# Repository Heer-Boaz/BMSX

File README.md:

# BMSX

BMSX is an emulated machine with real emulator discipline.

BMSX is documented and implemented as if it were an obscure physical console:
carts run against CPU, RAM/ROM, MMIO registers, and device controllers. Host
code exists to present audio, video, input, files, and platform entrypoints; it
should not become the cart-facing hardware contract.

The TypeScript implementation builds a JavaScript machine runtime plus browser
and Node hosts. The C++ implementation mirrors the machine structure and supplies C++ machine and host artifacts.

The technical manuals specify the console. See `docs/architecture.md` only for
internal software ownership, dependencies and host/tooling boundaries.

## Setup

- Node.js 22 or later
- `npm ci --include=dev`
- Linux/WSL native requirements: see the [first-build prerequisites](docs/programming/getting-started.md#prerequisites).

## First cartridge and hardware reference

Start with [Build and inspect example cartridges](docs/programming/getting-started.md)
for a visible GPU picture, source layout and project-tool commands. That companion
describes this repository, not a manufacturer-mandated SDK. The working manual
series separates three scopes:

- **Book I — System and Hardware Reference:** begin with the
  [System overview](docs/book1/console.md), then follow its links to the owning
  hardware chapters and [Memory and bus access](docs/book1/memory.md).
- **Book II — BLua32 and BIOS Reference:** begin with
  [CPU and BLua32 instructions](docs/book1/cpu.md),
  [BLua source programs and extensions](docs/book1/blua-programs.md), and
  [Program images and startup](docs/book1/program-images.md). BIOS services
  include [monitor diagnostics](docs/book1/bios-monitor.md). Cartridge source
  is not assumed to be ordinary Lua.
- **Book III — Cartridge and Expansion Reference:**
  [Cartridge sockets and mapped card devices](docs/book3/cartridge.md).

These are working drafts, not a complete or released console-reference series.

### Publishing the manuals

The Markdown books use [Quarto](https://quarto.org/docs/get-started/) 1.10.19 or
later with LuaLaTeX. Install Quarto, then its supported TeX distribution with
`quarto install tinytex`. On Ubuntu/WSL, SVG conversion and the publication fonts
are supplied by `sudo apt-get install librsvg2-bin fonts-liberation fonts-dejavu-core`.

From the repository root, build and publish locally with one command:

```sh
npm run manual:build
```

The PDFs are committed under `docs/pdf/` for direct viewing on GitHub:

- [Book I — System and Hardware Reference](docs/pdf/bmsx-book-i.pdf)
- [Book II — BLua32 and BIOS Reference](docs/pdf/bmsx-book-ii.pdf)
- [Book III — Cartridge and Expansion Reference](docs/pdf/bmsx-book-iii.pdf)

The complete generated publication is `dist/manual/`: `index.html` opens the
HTML reference, and `pdf/` contains the same three volumes linked from its
download menu. This directory stays outside Git and can be served or copied as
a whole. Native MathML and system fonts avoid font/formula CDNs. No GitHub build
or deployment is involved.

For local browsing, `npm run manual:preview` serves the HTML with live reload.
The [authoring guide](docs/manual/README.md) describes source conventions.

## Project Layout

- `machine/ts/machine`: TypeScript CPU, memory, MMIO bus, device controllers, program loader, and runtime lifecycle
- `machine/ts/common`: low-level shared helpers
- `machine/ts/audio`: host-side audio playback/output code, not the machine audio device
- `ide`: editor, terminal, workbench, and IDE runtime tooling
- `machine/bios`: the guest system-ROM source, organized by BIOS responsibility
- `cartlib`: independent cartridge software, not installed BIOS or firmware; linked into carts that choose to use it
- `hosts/browser`: browser player/product owners
- `hosts/node`: headless and CLI product owners
- `machine/cpp`: C++ machine/runtime implementation
- `hosts/libretro`: libretro core host entrypoint for BMSX
- `hosts/libretro_host`: local libretro frontend executable, an alternative to RetroArch
- `carts`: Lua cart software for the machine and cart-local resources
- `scripts/rompacker`: BIOS/cart compiler, linker, asset, and ROM builders
- `scripts/products`: deployable player, Studio, Node, and libretro product builders
- `scripts/bootrom`: Node player and tooling entrypoints
- `dist`: generated ROMs and runtime artifacts

## Build Model

- BIOS code lives in `machine/bios`
- BIOS assets live in `machine/bios/res`
- resident base, table, string, math, and OS modules live directly in `machine/bios`
- shared cart Lua lives in `cartlib`
- current carts live in `carts/<cart-folder>`
- current cart resources live in `carts/<cart-folder>/res`
- `build:toolchain:cart` takes the cart folder name, not the ROM manifest name
- headless/CLI use debug artifacts
- libretro/custom-host runs require non-debug BIOS and non-debug cart ROMs

## Architecture Doctrine

BMSX can be playful at the product level, but the machine layer is not a service grab bag. New cart-visible hardware should be represented as memory-mapped devices under `machine/devices`, with register addresses in `spec/bmsx/io`.

The technical manuals are the hardware and BIOS product specification; internal
architecture documentation is not another hardware reference. Machine ABI values such as register
addresses, status bits, IRQ flags, packet fields, opcodes, fixed-point words,
and device constants are numbers in that manual and in the owning TS/C++
machine constants. They are not fantasy-console convenience globals injected by
the emulator runtime.

Preferred direction for cart-visible features:

```text
cart Lua -> BIOS service or cart library -> MMIO/RAM -> machine device -> host output
```

Avoid this for new hardware-facing behavior:

```text
cart Lua -> C++ host/runtime shortcut
```

The host may accelerate implementation details, but it must not own the semantics of machine hardware. Use the architecture roles precisely: the machine owns cart-observable semantics, a host owns the embedding/process and physical services, and a mode is a behavior variant inside one host.

Current artifact names encode that split:

- `dist/libbmsx.js`: importable JavaScript machine/runtime library.
- `dist/engine.js`: IDE-free browser player/bootstrap with its statically linked runtime composition.
- `dist/studio.js`: browser Studio composition with IDE and compiler tooling.
- `libbmsx.a` in its CMake build tree: C++ machine/runtime.
- `dist/libretro_bmsx.so`: libretro core built around the C++ machine runtime.
- `dist/host_headless.js` and `dist/host_cli.js`: IDE-free Node player modes with their statically linked runtime composition.
- `dist/host_headless_tooling.js`: Node timelines, captures, scenario tests, IDE tests, and profiling.

## Timing integration

Machine scheduling is independent of host pacing, UI pause and output transport.
The device owners supply emulated deadlines; hosts admit execution and present
completed output through their existing frame owners. Installed clocks, reset
settings and programmable video timing belong in the [console](docs/book1/console.md)
and [PCRTC](docs/book1/pcrtc.md) references, not a second table in this README.

## Common Commands

Build BIOS debug artifacts:

```bash
npm run build:toolchain:bios -- --debug --force
```

Build a cart debug ROM:

```bash
npm run build:toolchain:cart -- pietious --debug --force
```

ROM builds share immutable, content-addressed output bytes in `.bmsx/builds`.
Exports in `dist` remain independent writable copies. Retention keeps only explicitly
owned output: the current selected result per build configuration, open build-backed
Studio sessions, current exports and published browser packages. Selecting a cached
result updates its current slot regardless of the file's publication date. Receipt
and log history does not retain ROM files; collected output is no longer offered
for opening Studio. The workspace server collects on startup
and after its build queue drains; CLI builds collect when no server owns the store.

Existing stores can first admit their existing exports/publication receipts and
inspect deduplication or collection without changing artifact contents:

```bash
npm run build:store -- deduplicate --publication-root .bmsx/hosting --export-root dist
npm run build:store -- collect --publication-root .bmsx/hosting --export-root dist
```

Add `--apply` to perform the selected operation. Offline collection requires the
workspace server to be stopped: its exclusive ownership protects active sessions,
including sessions in older server versions. Maintenance never removes the
publication/export directories, authored files or source recovery records.

Build the browser player:

```bash
npm run build:product:browser-player -- --debug --force
```

Build browser Studio:

```bash
npm run build:product:browser-studio -- --debug --force
```

Build the headless player or the separate validation tooling:

```bash
npm run build:product:node-headless-player -- --debug --force
npm run build:product:node-headless-tooling -- --debug --force
```

Force-build headless + BIOS + cart and run:

```bash
npm run headless:forcebuildallrun -- pietious
```

Run an already-built cart in headless mode:

```bash
npm run headless:game -- pietious
```

Run render parity through the TypeScript and C++ headless runtimes:

```bash
npm run test:render-parity
```

Run selected Node tests (TypeScript is supported):

```bash
npm test -- tests/lua/actor_runtime_tools.test.ts
npm test -- --test-name-pattern='Visual placement composes physical' tests/lua/affine_visuals.test.ts
```

All test scripts use `scripts/test.sh`: a shared cgroup v2 `memory.max` cap of
**at most 8 GiB** for the test process and its ordinary subprocesses. Existing
stricter caps stay untouched. Nested runners share that budget; Node suites
default to one test file at a time.
Build steps preceding the harness in npm scripts run separately; ordinary children
inherit the harness budget.
For a custom harness use `npm run test:exec -- <command> [arguments...]`.

Linux/WSL needs cgroup v2 memory control. By default, without an opt-in mode, the
runner accepts a verified current or ancestor `memory.max` of at most 8 GiB,
including a read-only container namespace root. Its existing swap and OOM settings
are inherited, not admission requirements. Only when no accepted cap exists does
the runner install a new 8 GiB cap through a delegated writable cgroup or systemd
(254 or newer) with a running user manager. Newly installed test cgroups also
disable swap and enable group-wide OOM termination.

A container therefore needs either an accepted host-installed cap or delegated
memory-controller access, not systemd as its init process. A read-only mount with
an unlimited or greater-than-8-GiB cap does not suffice. If the runner cannot
verify an accepted cap or install one, it refuses the run; `prlimit`, `ulimit` and
V8 heap limits are not substitutes for a shared process-tree memory budget.

For direct delegation, the host must provide an empty, writable parent cgroup
with the memory controller available to its subtree and `cgroup.kill` support.
This path also requires Python 3 (standard library only); inherited-budget and
systemd paths do not.
Select the delegated parent explicitly:

```bash
BMSX_TEST_CGROUP_PARENT=/sys/fs/cgroup/bmsx-tests npm test -- tests/platform/test_runner.test.mjs
```

The same variable works with `npm run test:exec -- <command> [arguments...]`.
The runner enables the memory controller, creates a private bounded child and
cleans it up; it does not move other host tasks. An already verified inherited
budget takes precedence, so nested invocations still share the original budget.
Failure to use an explicitly selected parent fails the run, not into another
launch mode. A host-prebounded container needs no writable cgroup mount.

This limits the test cgroup, not the entire agent or user session. Direct commands
and processes requesting their own systemd units (including browsers and native
process-scope tests) can run outside it; this is a guardrail, not a sandbox.

Run an explicit scenario test:

```bash
npm run headless:test -- pietious tests/carts/pietious/pietious_enter_world_assert.lua
```

Important:

- `headless:forcebuildallrun` and `headless:game` take the cart folder name
- `test:render-parity` force-builds and compares the render test carts through TS headless and the C++ libretro host
- headless runs `dist/host_headless.debug.js` with `dist/system/bmsx-bios.debug.rom`; it does not dynamically load `dist/libbmsx.debug.js`
- `headless:tooling` runs the separate `dist/host_headless_tooling.debug.js` validation product
- scenario tests are always explicit; `headless:game` does not auto-load assert modules
- the ordinary player never scans `tests/` or auto-loads `<cart>_demo.json`
- headless tooling timelines run unpaced, so the full scenario completes as fast as the emulator can simulate it
- `headless:test` and `headless:forcebuildalltest` are the explicit scenario-test paths
- Lua scenario tests run through the shared
  `ide/workbench/contrib/scenario_lab/execution_service.ts` owner; the headless
  host only adapts that owner to its frame and capture lifecycle. The packaged
  Lua API exposes `host.press(code, ticks)`, `host.down(code)`,
  `host.up(code)`, `host.at(tick, command)`, `host.capture(label)`, and
  `host.log(message)` for logical-tick input schedules

## Libretro / Custom Host

Libretro requires non-debug BIOS and non-debug cart ROMs. Do not run it against `*.debug.rom`.

Build the non-debug BIOS and cart ROM:

```bash
npm run build:toolchain:bios -- --force
npm run build:toolchain:cart -- pietious --force
```

Build the libretro core:

```bash
npm run build:product:libretro-wsl
```

Build the custom WSL libretro host:

```bash
npm run build:libretro-host-wsl:debug
```

Run the custom libretro host:

```bash
npm run run:libretro-host:wsl:headless -- ./dist/pietious.rom
```

Important:

- `run:libretro-host:wsl:headless` now runs silently by default with `SDL_VIDEODRIVER=dummy` and `SDL_AUDIODRIVER=dummy`
- the headless libretro-host path also passes `--no-audio`, so bare-metal smoke runs do not depend on an SDL or ALSA audio sink
- the silent SDL path uses the software backend on purpose
- the libretro core loads `dist/system/bmsx-bios.rom`, not `dist/system/bmsx-bios.debug.rom`
- the ROM argument must be the non-debug cart ROM, for example `./dist/pietious.rom`
- the custom libretro host falls back to `tests/carts/<cart>/<cart>_demo.json` when no explicit timeline is provided
- libretro timelines also run unpaced while the input timeline is active

## Input Timelines And Screenshots

- headless and the custom libretro host both support input timeline playback
- you do not need a separate `smoke` timeline
- timeline JSON files may include `capture: true` markers
- both runners execute the full chosen timeline; “fast” means they do not pace it to realtime
- screenshots are written to a `screenshots/` subfolder next to the timeline file
- timeline frame `N` is the boundary after accepted frontend presentation `N`; its input affects the next accepted presentation and a capture records that same next presentation under marker `N`
- the presentation clock starts at content load and counts BIOS output too; it does not inspect cart startup state
- when a cart folder name differs from the generated ROM filename, use `--rom-folder <cart-folder>` or an explicit `--input-timeline <file>` when running the custom libretro host manually

## ROM Inspection

`scripts/rominspector/rominspector.ts` is a CLI for inspecting a built `.rom`
file. It reads the raw ROM, parses the cart header and TOC, and reports asset
layout, manifest, and physical BLua32 details. This is the tool for confirming
the `bmsx/assets` address/length symbols and the rest of the ROM layout without
disassembling by hand.

Run it directly with `tsx`:

```bash
npx tsx scripts/rominspector/rominspector.ts dist/nemesis_s.debug.rom --list-assets
```

Options:

- `--list-assets` print the asset table to stdout (id, type, path, size, and
  buffer/metabuffer start/end offsets in hex); this is the default when no other
  output flag is given
- `--manifest` print the cart manifest (and project root path) as JSON
- `--blua32-asm` print the physical BLua32 disassembly and exit; source-line
  comments are included when the ROM is not stripped
- `--asset-symbols` print the generated `bmsx/assets` ROM address symbols
- `--cycle-cost` print a BLua32 cycle-cost analysis
- `--ui` / `--ui-native` open the interactive native inspector UI

The header line printed on every run shows header/manifest/toc/data/metadata
offsets and lengths plus the BLua32 image range, physical startup/IRQ/exception
function addresses, and static-layout token, so the section layout is visible
at a glance.

## Notes

- `build:toolchain:cart` means “build a BLua cartridge ROM”
- cart folder resolution is `carts/<name>`
- old TypeScript full-game projects were removed instead of being kept as compatibility fallbacks
- the last complete branch that still contains the old TypeScript full-game runtime lives at `archive/ts-full-engine`

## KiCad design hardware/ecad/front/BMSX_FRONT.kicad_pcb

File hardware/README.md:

# BMSX hardware

Editable electrical and mechanical sources for the reference console, with
physical interface RTL and directed simulations. The manufacturer-facing
technical and service reference starts at [Book IV](../docs/book4/index.md).
Books I–III remain the programmer-visible product specification.

## Source layout

| Directory | Contents |
|---|---|
| `ecad/mainboard/` | KiCad mainboard, hierarchical schematic, rules and local libraries |
| `ecad/mainboard_memory_candidate/` | Memory-expansion schematic and unrouted PCB candidate; pad nets synchronized |
| `ecad/mainboard_input_candidate/` | Separate INPUT-to-GFX and memory schematic/PCB candidate; pad nets synchronized, logic still proposed |
| `ecad/mainboard_passive_candidate/` | INPUT/memory candidate with the unused fan header removed; separate unrouted schematic and PCB |
| `ecad/gfx_wide_vram/` | Partial 64-bit VRAM interface schematic and local SRAM symbol; no PCB or U2 pin assignments |
| `ecad/gfx_vram_snapshot/` | Partial combined wide-VRAM and snapshot-memory schematic; no PCB or U2 pin assignments |
| `ecad/front/`, `ecad/keyboard/`, `ecad/av/` | KiCad connector daughterboards |
| `ecad/scart/` | Numbered Kycon socket and underside loom joints on a separate contact board; copper not routed |
| `models/` | Component geometry and catalogue identities |
| `design/` | Mechanical dimensions and numerical analysis inputs |
| `cad/` | Parts, assemblies, interference checks and native illustrations |
| `rtl/`, `tests/` | Memory controllers/schedulers, SYS/CAD arbitration, APU ROM reader, U7 ROM/input, keyboard, pad/accessory, display-context and event circuits and tests |
| `tools/` | Native board metadata, engineering analyses and release packaging |
| `build/` | Generated geometry, exports, illustrations and test results |

KiCad supplies component positions and board geometry. CAD consumes those
positions; it does not maintain a second editable placement model. Cartridge
polarising keys are integral to the internal metal frame, with matching returns
in the card shell. Their contact pattern and PCB holes remain connector-defined.
Native builds do not modify these sources or use an earlier delivery as input.
The packaging tool can explicitly repackage an extracted delivery without
rebuilding its artifacts; that operation does not qualify them again.

The native `BMSX_COMPACT_board_assembly.step` is the bare board in its assembly
position, despite its name. `BMSX_COMPACT_components.step` contains the
component placement models separately, including the conceptual J500 header.
`BMSX_PASSIVE_CANDIDATE_board_native.step` is the separate bare-board export of
the passive candidate PCB; it contains no component models and is not a new
complete assembly or a routing or fit qualification. Its exported solid is
1.46 mm thick, whereas the PCB's nominal stackup is 1.6 mm. Treat the STEP as
the KiCad board-body representation, not as a finished thickness measurement.
`BMSX_WIDE_GFX_CLUSTER_CONCEPT.step` is a separate placement study using the
current bare-board geometry, U1 and cartridge-socket geometry from the retained
assembly, and existing memory models translated to the U152/U153 snapshot
positions. These are retained reference models, not newly obtained vendor
models. The U2 and four proposed VRAM positions are thin coloured plan markers,
not component models, package heights or footprints.
Other board components, routing, the deck and cooling are omitted. The model
does not establish clearance, fit, electrical behaviour, timing or a complete
assembly; in particular, the proposed underside marker still conflicts with the
existing TP4 through-hole until an actual PCB change is designed.
`BMSX_WIDE_VRAM_PARTIAL_A3_schema.pdf` and its XML netlist export the separate
four-SRAM interface schematic. Its SRAM pin numbers follow the 1993 Micron
MT5LC256K16D4 data sheet; U2 connections are logical labels, not assigned ASIC
pins. Snapshot memory, supply decoupling, timing and integration are not part
of this partial schematic. It does not replace the mainboard schematic.
`BMSX_GFX_VRAM_SNAPSHOT_PARTIAL_schema.pdf` and its XML netlist export a
separate hierarchy combining copies of that wide-VRAM sheet and the existing
snapshot-memory and support sheets. The banks share the lower data lines,
address and control signals, but retain separate chip selects. The new VRAM
bank's supply decoupling and control pull-ups, U2 pin assignments and bank
selection logic, timing, and PCB integration remain open. This is not a complete
mainboard schematic or evidence of electrical or timing qualification.
The restored STEP referenced by the J500 KiCad footprint is its own conservative
maximum-envelope model, not a manufacturer model or a qualified mating shape.

`reference/accessories-a04/` retains original detached-keyboard and cartridge
source extracts, design notes and the two game-title images from the A04 handover.
`build/exports/BMSX_KEYBOARD_A04_REFERENCE.step` and
`BMSX_CARTRIDGES_A04_REFERENCE.step` are the corresponding earlier native
models, not regenerated assemblies or proof of fit with the current console.
The A04 notes also describe an older power-supply example; the current console
power and connector description in Book IV takes precedence. The source extract
is not a complete standalone reconstruction of the A04 package, whose original
remains in the preserved BMSX work handover.

## Release scope

This is a digitally assembled reference construction, not a fabricated or
powered console. The mainboard is intentionally unrouted. The proposed
four-device integration places INPUT in U2 GFX, but the combined logic and
complete event path are not implemented. The private DRAM devices U150/U151
are on the separate candidate PCBs, not the original board; their presence does
not qualify a physical runtime capacity. The native CPU/interpreter, complete
GFX and APU, power and thermal behavior, and connector fit remain unqualified.
The approved timing and audio directions are collected in
[the specification proposals](../docs/proposed-specification-changes.md), not
silently adopted in Books I–III or the emulator.

A diagnostic service-transport candidate uses a U1 user data register in the
J302 scan chain to expose whether a completed diagnostic byte is available and
its value, with an explicit consume request. An incomplete or unacknowledged
scan must not consume or repeatedly advance a byte; the scan and CORE clock
domains need a handshake. The register, handshake and full chip-to-chip scan
chain are not integrated, and reset and disconnect behavior remain open. The
software-visible queue contract is specified in
[Book I](../docs/book1/system.md#sec-system-diagnostic-text-output); the
proposed service connection is described in Book IV.

The passive candidate removes the unused fan header. The separate
`build/exports/BMSX_COMPACT_PASSIVE_SPREADER_KEYBOARD_console.step` combines
that board placement with flat-spreader and keyboard-front proposals against
retained assembly geometry. It is not a newly qualified complete assembly.
The separate rear presentation uses illustrative connector faces, not
manufacturer CAD or evidence of mating or mounting.
`BMSX_CONSOLE_COMPLETE_VISUAL_PRESENTATION.step` combines those illustrative
rear faces with the console and both MSX-style reference cartridges. It is a
presentation model, not a full connector, mating or assembly qualification.
The separate `BMSX_CONSOLE_ALL_FACES_VISUAL_PRESENTATION.step` also adds an
illustrative keyboard socket face to that presentation. Its contact markings
and the rear connector faces are not manufacturer models or working contacts.

The separate `BMSX_CARTRIDGE_PROTECTIVE_SKIRT_CONCEPT.step` explores a
cartridge lip and matching frame channels to open the dust doors before the
board reaches them. The separate
`BMSX_COMPACT_PROTECTIVE_SKIRT_FRAME_console.step` incorporates those frame
channels into the empty keyboard/spreader console candidate; the original
console STEP is retained. The separate
`BMSX_CONSOLE_TWO_CARTRIDGES_SKIRT_CONCEPT.step` shows both modified
cartridges seated with the corresponding leaves and springs open. Sampled
insertion poses and the console exports do not
constitute continuous-motion, complete assembly, strength or manufacturing
qualification.

The `BMSX_CARTRIDGE_MSX_SKIRT_CONCEPT.step` and
`BMSX_CONSOLE_TWO_MSX_SKIRT_CARTRIDGES_CONCEPT.step` variants use the
MSX-inspired cartridge shell styling with the same proposed skirt and frame;
they are the provisional reference cartridge construction. The earlier
plain-shell variants remain available; reports retain the source hashes from
their own export runs.

`BMSX_PAD_PLUG_REINFORCED_NOSE_CONCEPT.step` is the proposed connector
construction with stepped cavities, terminal envelopes and a wider plug nose.
It does not model spring deflection, electrical contact or a qualified cable
restraint. The earlier narrow-nose and empty-channel plug STEPs remain available.

The memory, INPUT and passive candidate PCBs have since had their schematic
pin names, electrical types and component values synchronized. A native KiCad
save was compared with each preceding board: only these metadata fields changed,
not nets or geometry. Earlier placement and console-assembly reports retain the
preceding board hashes; they are historical evidence, not reports regenerated
from the metadata-corrected files. The geometry-only STEP and images remain the
same; this comparison does not constitute a new assembly qualification. The
focused candidate-placement screen compares the current passive PCB against
the retained pre-metadata native board in `build/exports/` and verifies that
its non-metadata text is unchanged before using the historical placement.

The inherited DRC rule profile remains unchanged, including its existing five
ignored footprint and courtyard metadata checks; no new findings are
suppressed. Native reports include the incomplete connectivity, and `make drc`
fails while copper routing remains unfinished. See the result's scope and
input hashes before applying any older check to changed sources.

## Focused workflow

Run commands from `hardware/`. For a documentation-only change, update the
Markdown manuscript without regenerating CAD, illustrations, ERC or RTL:

```sh
make build/exports/BMSX_technical_reference.md
```

For the wide-GFX cluster study, first export a current bare board and placement
report with the KiCad environment active. Use a new output name or preserve the
previous result; the study refuses to overwrite its export or report. This
example requires a new intermediate directory and new output paths:

```sh
test ! -e build/cad/gfx_wide_cluster && \
  mkdir -p build/cad/gfx_wide_cluster && \
python3 tools/mainboard.py --board ecad/mainboard_passive_candidate/BMSX.kicad_pcb \
  --output build/cad/gfx_wide_cluster/current_board.json && \
kicad-cli pcb export step --board-only --min-distance 0.000001mm \
  -o build/cad/gfx_wide_cluster/current_board.step \
  ecad/mainboard_passive_candidate/BMSX.kicad_pcb && \
env -u PYTHONPATH .venv/bin/python cad/gfx_wide_cluster.py
```

The retained assembly report and its BReps are also required. The fresh
bare-board STEP has no copper or components; the geometry owner reconstructs
its nominal finished thickness from the KiCad stackup. These commands neither
run DRC nor qualify the conceptual reservations. With the same intermediates,
run the CAD script directly with new `--output` and `--report` paths to retain
the earlier result.

The standard Quarto Book IV profile can also render a browsable HTML reference
without generating PDF or rerunning hardware checks. From `hardware/`, choose
a new project-local output directory and a new export directory so that an
earlier export is not overwritten. Quarto's output directory must remain under
`docs/`, where it can safely manage its own generated files:

```sh
test ! -e ../docs/_book-iv-example && \
  test ! -e build/exports/BMSX_BOOK_IV_HTML_EXAMPLE && \
  (cd ../docs && quarto render . --profile book-iv --to html \
    --output-dir _book-iv-example) && \
  cp -a ../docs/_book-iv-example build/exports/BMSX_BOOK_IV_HTML_EXAMPLE
```

Keep the relative figure and stylesheet files alongside the HTML. For browser
search and scripts, serve the directory over loopback HTTP rather than opening
it through `file://`:

```sh
python3 -m http.server 8000 --bind 127.0.0.1 --directory build/exports/BMSX_BOOK_IV_HTML_EXAMPLE
```

Then open `http://127.0.0.1:8000/`. A later render needs a different output
directory or explicit preservation of the previous export.

If a figure changed, regenerate its specific target in `cad/targets.mk` and
copy the current source and rendered figure to `build/exports/figures/` before
packaging. For example, this renders only the cartridge-insertion view:

```sh
EGL_PLATFORM=surfaceless env -u PYTHONPATH .venv/bin/python cad/render_console.py --publication-dir build/publication --view insertion
```

Individual targets, including optional CAD and RTL work, can be inspected with
`make help` and in the Makefiles. Examples:

```sh
make passive-spreader-keyboard-console  # separate console STEP candidate
make check-combined-candidate-placement # focused nominal placement screen
make cartridge-protective-skirt-concept # separate lip/frame concept and pose screen
make protective-skirt-frame-console     # frame channels in the retained console STEP
make protective-skirt-seated-console    # both candidate cartridges seated
make cartridge-msx-skirt-concept        # MSX-styled shells and skirt
make msx-skirt-seated-console           # both MSX-styled cartridges seated
make complete-console-presentation       # seated cartridges and illustrative rear faces
make keyboard-socket-face-illustration   # illustrative front keyboard socket face
make all-faces-console-presentation      # keyboard and rear presentation faces
make pad-plug-contacts-concept           # separate pad contact/enclosure concept
make pad-plug-reinforced-nose-concept    # wider nose candidate, same socket and contacts
make rear-console-presentation          # separate illustrative rear STEP
make check-scart                        # contact-board ERC and native DRC
make check-memory                       # memory waveform integration tests
make check-pad                          # serial link and APPLY tests
make check-cart-reference               # reference card pin paths
make drc-reports                        # native findings, including unrouted nets
```

Some targets rely on previously generated inputs and compare actual owners in
the full repository. The selected-source delivery is not a complete runtime or
CMake checkout. In particular, `make check-cart-pin-contract` is an intentionally
failing conformance check for the candidate's fast IRQ reassertion, not a
passing reference-card check. A passing focused test proves its stated case,
not the entire physical console or production qualification.

Full batches (`make native`, `make check`, and `make manuscript`) are optional.
`make manuscript` depends on `publication` and can regenerate many images;
use the specific manuscript target above for text-only changes.

**Do not run `make clean` without first preserving the required results.** It
removes the entire `build/` directory, including native exports, retained
geometry, reports and test evidence as well as intermediate files. Some results
record earlier sources or investigations and are not replaced by packaging the
current tree. Preserve needed results in a verified delivery first. Sources
and earlier deliveries are not removed by this target.

## Tools

The reference workflow uses Python 3.12 for CAD; KiCad 9.0.8 with its matching
`pcbnew` Python for EDA; GNU Make 4.4; Icarus Verilog 12; Yosys 0.52; Node 22
with esbuild 0.28.1; and C++20 for focused comparisons with existing runtime
owners. `rsvg-convert` provides PNG previews of SVG figures. Install the CAD
dependencies from the pinned closure and keep the KiCad Python environment
separate:

```sh
uv venv --python 3.12 .venv
uv pip sync --python .venv/bin/python requirements.txt
kicad-cli version
python3 -c 'import pcbnew; print(pcbnew.GetBuildVersion())'
```

If KiCad is an extracted local installation, load its existing environment in
the shell before checking its CLI and Python binding. The local environment
script is not included in the delivery. `requirements.in` is the source for
updating `requirements.txt` with `uv pip compile`. Make variables such as
`CAD_PYTHON`, `KICAD_CLI`, `KICAD_PYTHON`, `IVERILOG`, `VVP`, `YOSYS`, `NODE`,
`TSX` and `ESBUILD` select tool locations; CAD recipes remove `PYTHONPATH`.

## Component sourcing

The reference SCART contact board and carrier are based on the numbered Kycon
K-SCART-021 drawing. The related K-SCARTX-021 discontinuation notice does not
establish the status of the original part; its procurement is unconfirmed.
The following inquiry alternatives are retained for engineering, not approved
drop-in replacements. Check current supplier availability and verify a
candidate's complete contact mapping and mechanical fit before adopting it.

The [Foxconn RS11121-H01-4F](https://www.fit-foxconn.com/w73/fit/image/Products/Spec/Spec/RS11121-H01-4F.pdf)
is a sourcing candidate, not an approved replacement. Its manufacturer drawing
specifies a lead-free code and shows the same nominal 65.80 mm front width,
58.40 mm mounting-ear spacing, 16.50 mm face height, 3.81 mm row pitch and
5.08 mm row separation as the Kycon reference. Its stated contact staggering
is 1.91 mm rather than 1.905 mm; the 3 mm-wide boardlock openings have a
50.05 mm inner separation instead of 49.80 mm. The Foxconn drawing does not
identify its PCB view or number its tails, and does not specify the contact
drill or mounting-ear bore diameter. These dimensional similarities do not
establish the electrical pin mapping or full assembly fit. Obtain a numbered
manufacturer drawing or verify all 21 face-to-tail connections and mechanical
dimensions on the actual part before using it with the reference board and
carrier. A [supplier listing](https://tonarism-online.jp/item/index.php?cnt=&maker=FOXCONN&now=18)
offers the exact part number for quotation; listing inventory is not a
confirmed order, authenticated lot, or commitment to supply. A separate
[Electrokit listing](https://www.electrokit.com/en/scart-kontakt-hona-21-pol-pcb)
listed 26 generic right-angle PCB sockets when checked on 27 October 2026,
but does not identify a maker or part number. It is a possible sample source,
not confirmation of Kycon availability or a qualified replacement. Before
approving an alternative, identify its manufacturer, part and lot; verify
all 21 face-to-tail connections and unintended shorts, measure its mounting
datums, and test the assembled analogue path.

[BKL 0903018](https://www.bkl-electronic.de/scart-einbaubuchse-printmontage-900-0903018)
is a further manufacturer-listed 21-contact right-angle inquiry candidate, not
an approved drop-in. Its [manufacturer drawing](https://www.bkl-electronic.de/media/cb/28/55/1774056840/0903018.pdf?ts=1774056840)
shows 2.54 mm between contact rows and 1.5 mm contact holes, versus 5.08 mm
and 1.3 mm in the existing Kycon-based contact-board footprint. Its stated
nominal mounting-ear pitch is 58.5 mm versus 58.4 mm for the reference.
It would therefore need a revised footprint and a checked pin-to-face map;
the drawing does not number the contacts. The product inquiry page does not
confirm available stock, delivery or a qualified replacement.

## Implementation references

The proposed shared audio schedule and retained decode/interpolation buffers
were compared with the working FPGA implementations in
[PSX MiSTer's SPU](https://github.com/MiSTer-devel/PSX_MiSTer/blob/cd17b5a0ad261005c321d9d5ba41b8dbe313a7d3/rtl/spu.vhd#L1456-L1678)
and [SNES MiSTer's DSP](https://github.com/MiSTer-devel/SNES_MiSTer/blob/bdcd33c5cab652109eeb7c695910b77b6f21df2f/rtl/DSP.vhd#L574-L685).
Their codec semantics, RAM arrangements and demonstrated throughput are not BMSX
contracts or proof of this proposal's timing.

The serial receiver design was checked against
[QMK's PS/2 implementation](https://github.com/qmk/qmk_firmware/blob/master/drivers/ps2/ps2_interrupt.c)
and [OpenTitan's UART receiver](https://github.com/lowRISC/opentitan/blob/master/hw/ip/uart/rtl/uart_rx.sv).
The Set-2/HID correspondence follows Microsoft's
[USB HID to PS/2 translation table](https://download.microsoft.com/download/1/6/1/161ba512-40e2-4cc9-843a-923143f3456c/translate.pdf)
and the BMSX keyboard usage reference. SPI sequencing follows explicit
shift-register/edge ownership, as in
[OpenTitan's SPI host](https://github.com/lowRISC/opentitan/tree/master/hw/ip/spi_host/rtl).
These are implementation references, not alternate BMSX specifications.

The flash sequencer was compared with the halfword capture/acknowledgement
organisation in [Milkymist's NOR controller](https://github.com/m-labs/milkymist/blob/master/cores/norflash16/rtl/norflash16.v).
Its 70 ns access and 20 ns output-disable limits come from the selected
[SST39VF6401B data sheet](https://ww1.microchip.com/downloads/aemDocuments/documents/MPD/ProductDocuments/DataSheets/SST39VF6401B-SST39VF6402B-64-Mbit-x16-Multi-Purpose-Flash-Plus-20005008.pdf).
The cartridge reference uses the same example flash. Microchip's
[2018 data-sheet revision](https://ww1.microchip.com/downloads/en/DeviceDoc/SST39VF6401B-SST39VF6402B-64-Mbit-x16-Multi-Purpose-Flash-Plus-Data-Sheet-DS20005008C.pdf)
marks it not recommended for new designs, while the manufacturer's
[product page](https://www.microchip.com/en-us/product/sst39vf6401b) lists it
in production. Confirm the status of the intended orderable part before any
present-day procurement; this does not change the BMSX card interface.
The complete-image size/fill boundary follows the image-producer organisation
used by [U-Boot binman](https://github.com/u-boot/u-boot/blob/master/tools/binman/etype/fill.py),
without adopting its container format or changing BMSX firmware bytes.
The event boundary uses the persistent-toggle/synchroniser/change-detection
organisation of [OpenTitan's pulse synchroniser](https://github.com/lowRISC/opentitan/blob/master/hw/ip/prim/rtl/prim_pulse_sync.sv)
and separates a momentary event from retained interrupt state, as in
[OpenTitan's interrupt primitive](https://github.com/lowRISC/opentitan/blob/master/hw/ip/prim/rtl/prim_intr_hw.sv).
Unlike a source-clock/pulse interface, U1 receives only the physical open-drain
request; a dedicated falling-edge event-clock leaf owns its source toggle.

The shared-bus arbitration was compared with
[GRLIB's AHB controller](https://github.com/TUT-ASI/leon3-grlib-gpl-mirror/blob/main/lib/grlib/amba/ahbctrl.vhd)
and [OpenTitan's multi-host socket](https://github.com/lowRISC/opentitan/blob/master/hw/ip/tlul/rtl/tlul_socket_m1.sv).
Frame-start reservation is before architectural acceptance, not a post-commit
retry or a copied AHB/SPLIT wire encoding. GFX fetch/decoded-stream ownership
follows the separation in
[LiteX's video reader](https://github.com/enjoy-digital/litex/blob/master/litex/soc/cores/video.py).

The memory boundaries were checked against
[LiteX's asynchronous SRAM core](https://github.com/enjoy-digital/litex/blob/master/litex/soc/cores/ram/async_sram.py),
[PULP's round-robin arbiter](https://github.com/pulp-platform/common_cells/blob/master/src/cc_rr_arb_tree.sv)
and OpenTitan's
[target steering](https://github.com/lowRISC/opentitan/blob/master/hw/ip/tlul/rtl/tlul_socket_1n.sv).
The selected [non-B IS41LV16100 data sheet](https://www.mouser.com/catalog/specsheets/issi_IS41C16100.pdf)
owns the SOJ42 pinout and DRAM limits. The SRAM limits come from ISSI's
[512K × 16](https://www.issi.com/WW/pdf/61-64WV51216.pdf) and
[256K × 16](https://www.issi.com/WW/pdf/61-64WV25616.pdf) BLL −10 grades.

## Delivery

After updating the relevant sources and generated artifacts, package the
existing build into a new destination:

```sh
.venv/bin/python tools/release.py --archive-only /absolute/path/to/new-delivery
```

Omit `--archive-only` to create the directory as well as the ZIP. In the
checkout, archive-only staging uses `hardware/build`; the extracted-delivery
mode stages beside its chosen destination. Avoid a tmpfs destination when the
archive is large. The ZIP is created exclusively and does not overwrite earlier
deliveries. Packaging copies editable sources, selected
comparison inputs, manuscript, figures, native exports and existing evidence.
It uses current reports and dependency metadata and does not regenerate or
qualify any of them. `SHA256SUMS` covers the payload. The packaged Books I–III
PDFs are existing exports, not rebuilt or checked for currency.

New deliveries also retain the compiler dependency files used by the collector.
To repackage an extracted delivery without rebuilding its existing exports or
evidence, run the script from that delivery and select its root explicitly:

```sh
python3 /absolute/path/to/extracted/source/hardware/tools/release.py \
  --from-delivery /absolute/path/to/extracted --archive-only /absolute/path/to/new-delivery
```

This repackages the extracted source and its existing artifacts; it does not
rebuild or requalify hardware. Earlier deliveries without the dependency files
cannot use this mode directly.

New packages also retain the existing CAD intermediates under `evidence/cad/`.
To copy the delivered exports, report files, CAD intermediates and compiler
depfiles into a new `source/hardware/build/` in an extracted delivery:

```sh
python3 /absolute/path/to/extracted/source/hardware/tools/release.py \
  --restore-build-from-delivery /absolute/path/to/extracted
```

The build directory must not already exist; no existing file is overwritten.
This duplicates the artifacts, so use a persistent volume with enough free
space, not `/tmp`. Deliveries without `evidence/cad/` can still be repackaged,
but this reconstruction refuses them. A copy operation that fails can leave a
partial new build directory for inspection; it does not delete anything. This
only restores the artifacts that were present when packaged: it neither runs a
build nor proves their currency, completeness or qualification.

The source subset in the delivery is not the full BMSX checkout. Rebuilding a
probe that depends on the full runtime requires that checkout and its own build
inputs. Preserve original and prior exports separately; packaging does not
create a new hardware qualification or make an earlier result current.

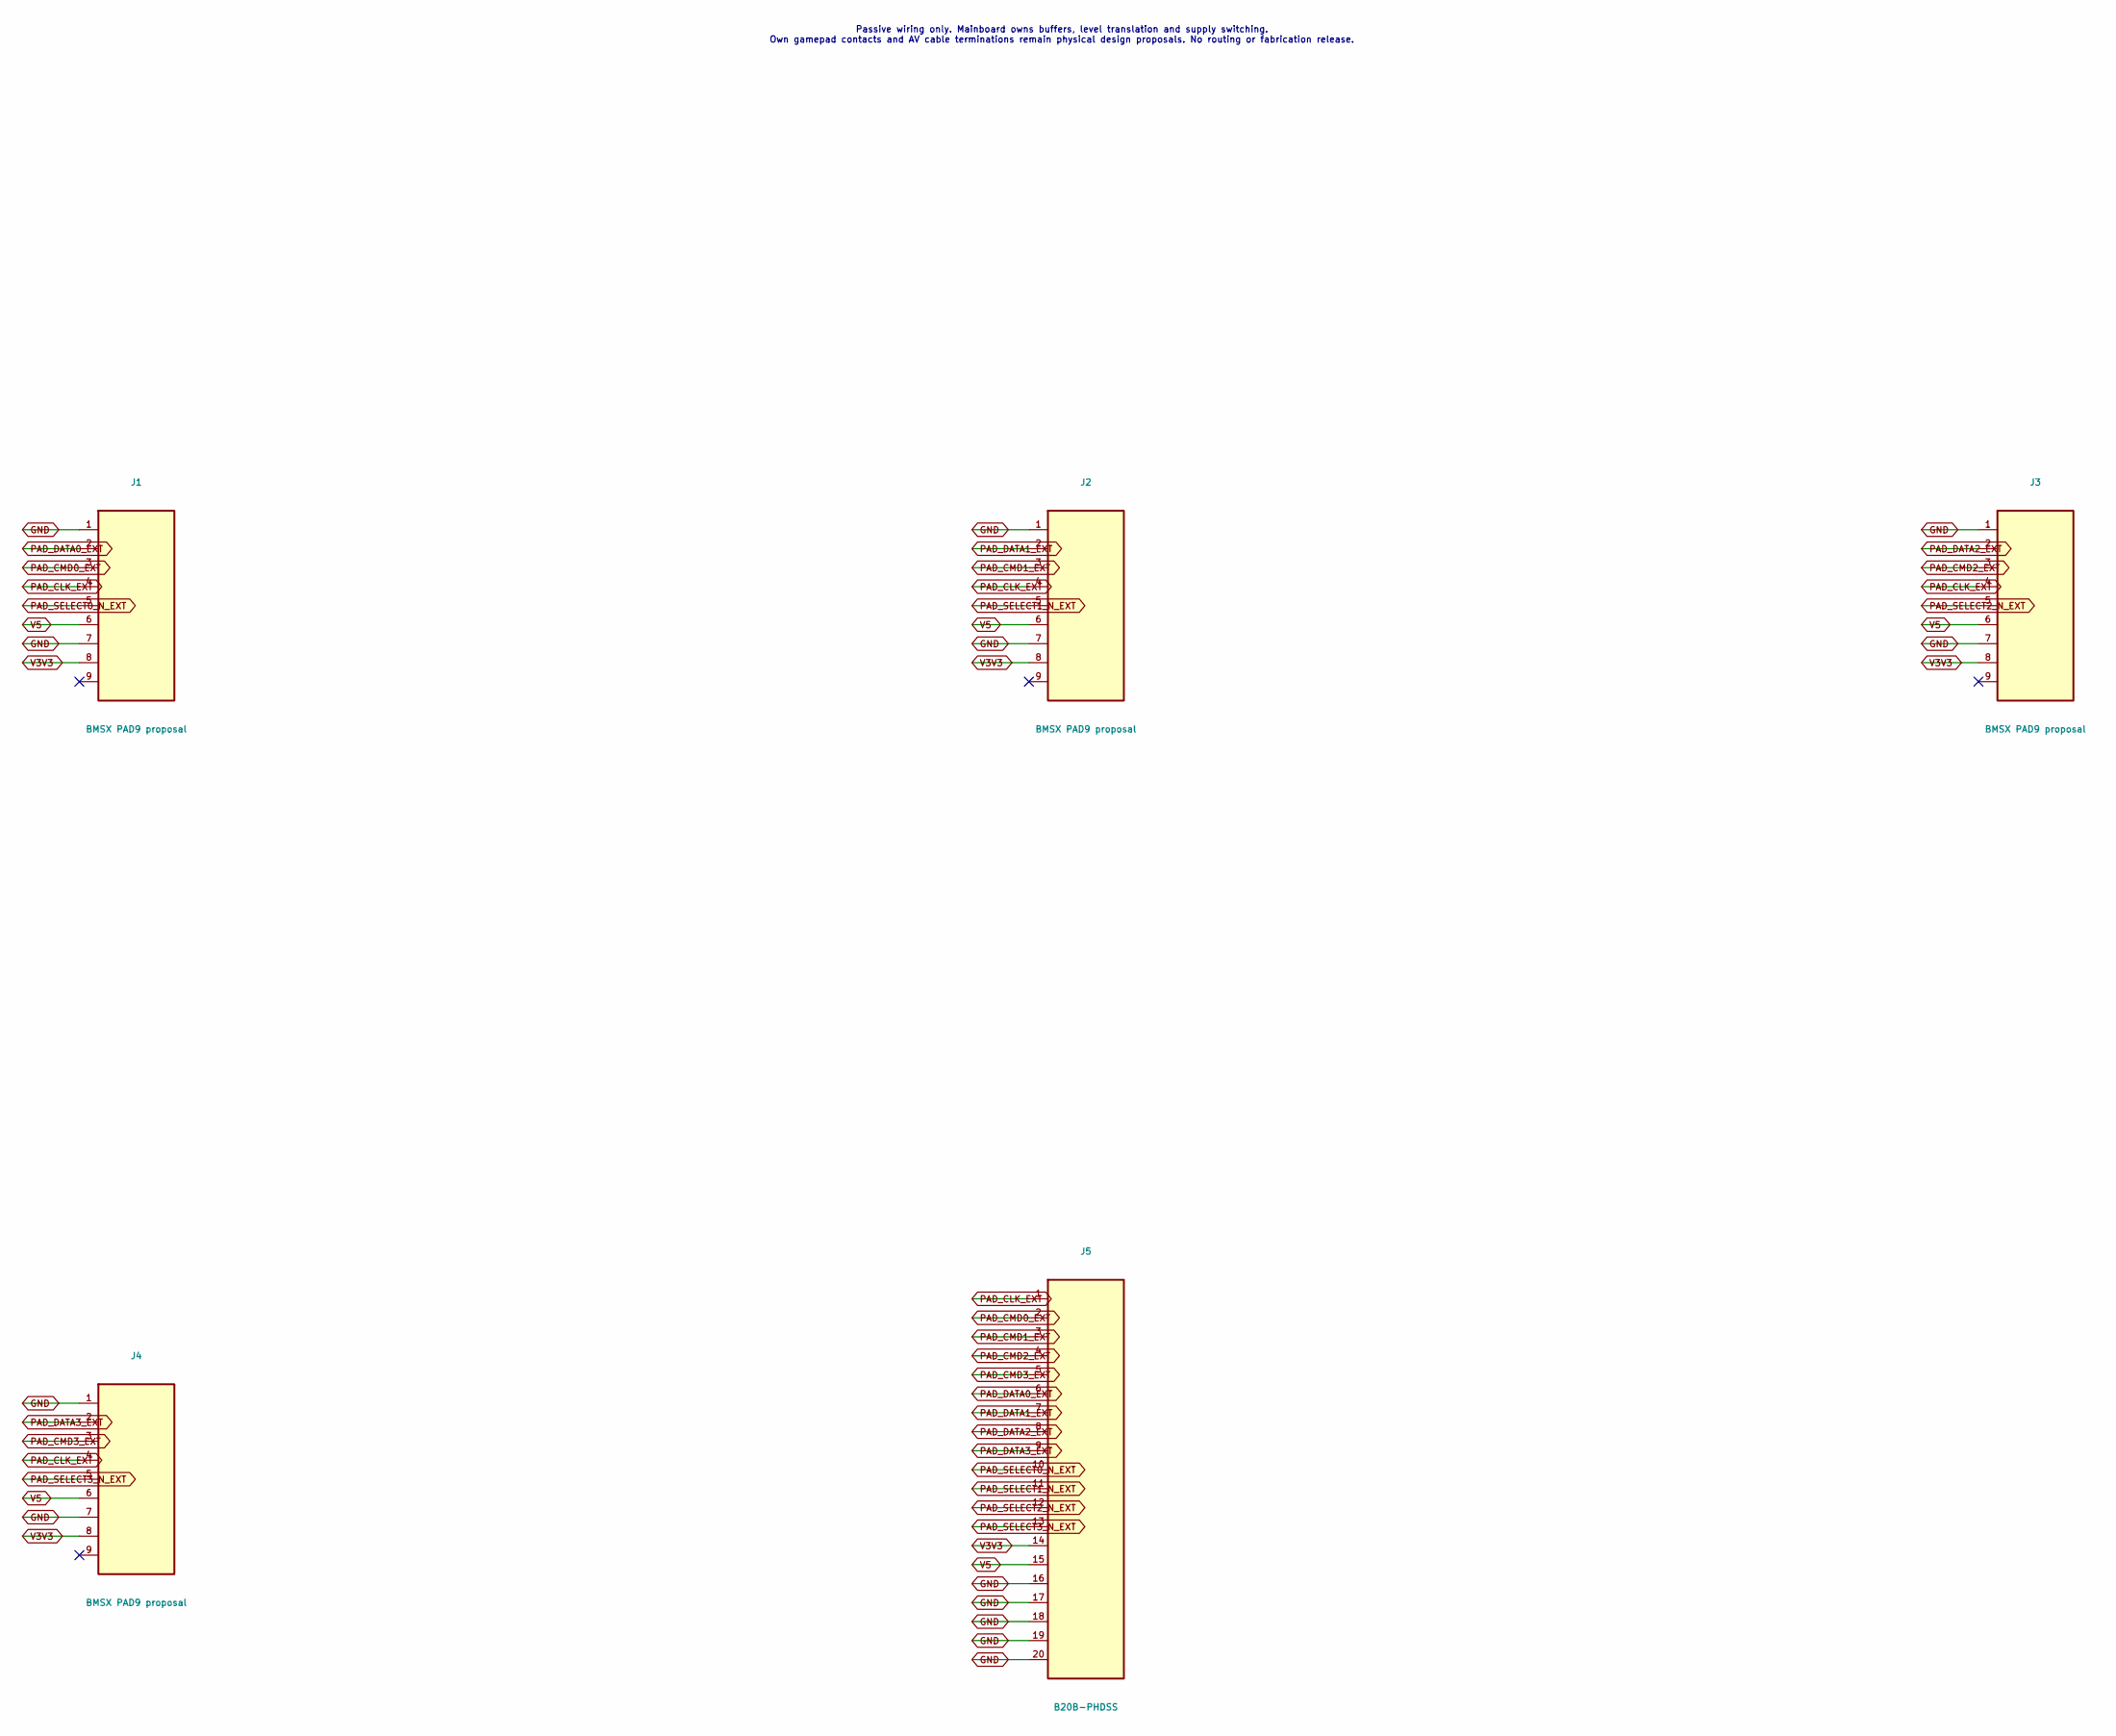
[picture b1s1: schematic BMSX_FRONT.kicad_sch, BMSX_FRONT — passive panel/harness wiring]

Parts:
J1, J2, J3, J4: BMSX PAD9 proposal; BMSX_PAD9
J5: B20B-PHDSS; JST_PHD_B20B-PHDSS_2x10_P2.00mm_Vertical; MPN B20B-PHDSS

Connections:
GND: J1.1, J1.7, J2.1, J2.7, J3.1, J3.7, J4.1, J4.7, J5.16, J5.17, J5.18, J5.19, J5.20
PAD_CLK_EXT: J1.4, J2.4, J3.4, J4.4, J5.1
PAD_CMD0_EXT: J1.3, J5.2
PAD_CMD1_EXT: J2.3, J5.3
PAD_CMD2_EXT: J3.3, J5.4
PAD_CMD3_EXT: J4.3, J5.5
PAD_DATA0_EXT: J1.2, J5.6
PAD_DATA1_EXT: J2.2, J5.7
PAD_DATA2_EXT: J3.2, J5.8
PAD_DATA3_EXT: J4.2, J5.9
PAD_SELECT0_N_EXT: J1.5, J5.10
PAD_SELECT1_N_EXT: J2.5, J5.11
PAD_SELECT2_N_EXT: J3.5, J5.12
PAD_SELECT3_N_EXT: J4.5, J5.13
V3V3: J1.8, J2.8, J3.8, J4.8, J5.14
V5: J1.6, J2.6, J3.6, J4.6, J5.15

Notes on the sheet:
Passive wiring only. Mainboard owns buffers, level translation and supply switching. Own gamepad contacts and AV cable terminations remain physical design proposals. No routing or fabrication release.

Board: 2 copper layers, 9 parts (0 on the bottom side), 16 nets, no tracks yet.

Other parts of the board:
H1, H2, H3: MountingHole_3.4mm
H4: MountingHole_8.2mm

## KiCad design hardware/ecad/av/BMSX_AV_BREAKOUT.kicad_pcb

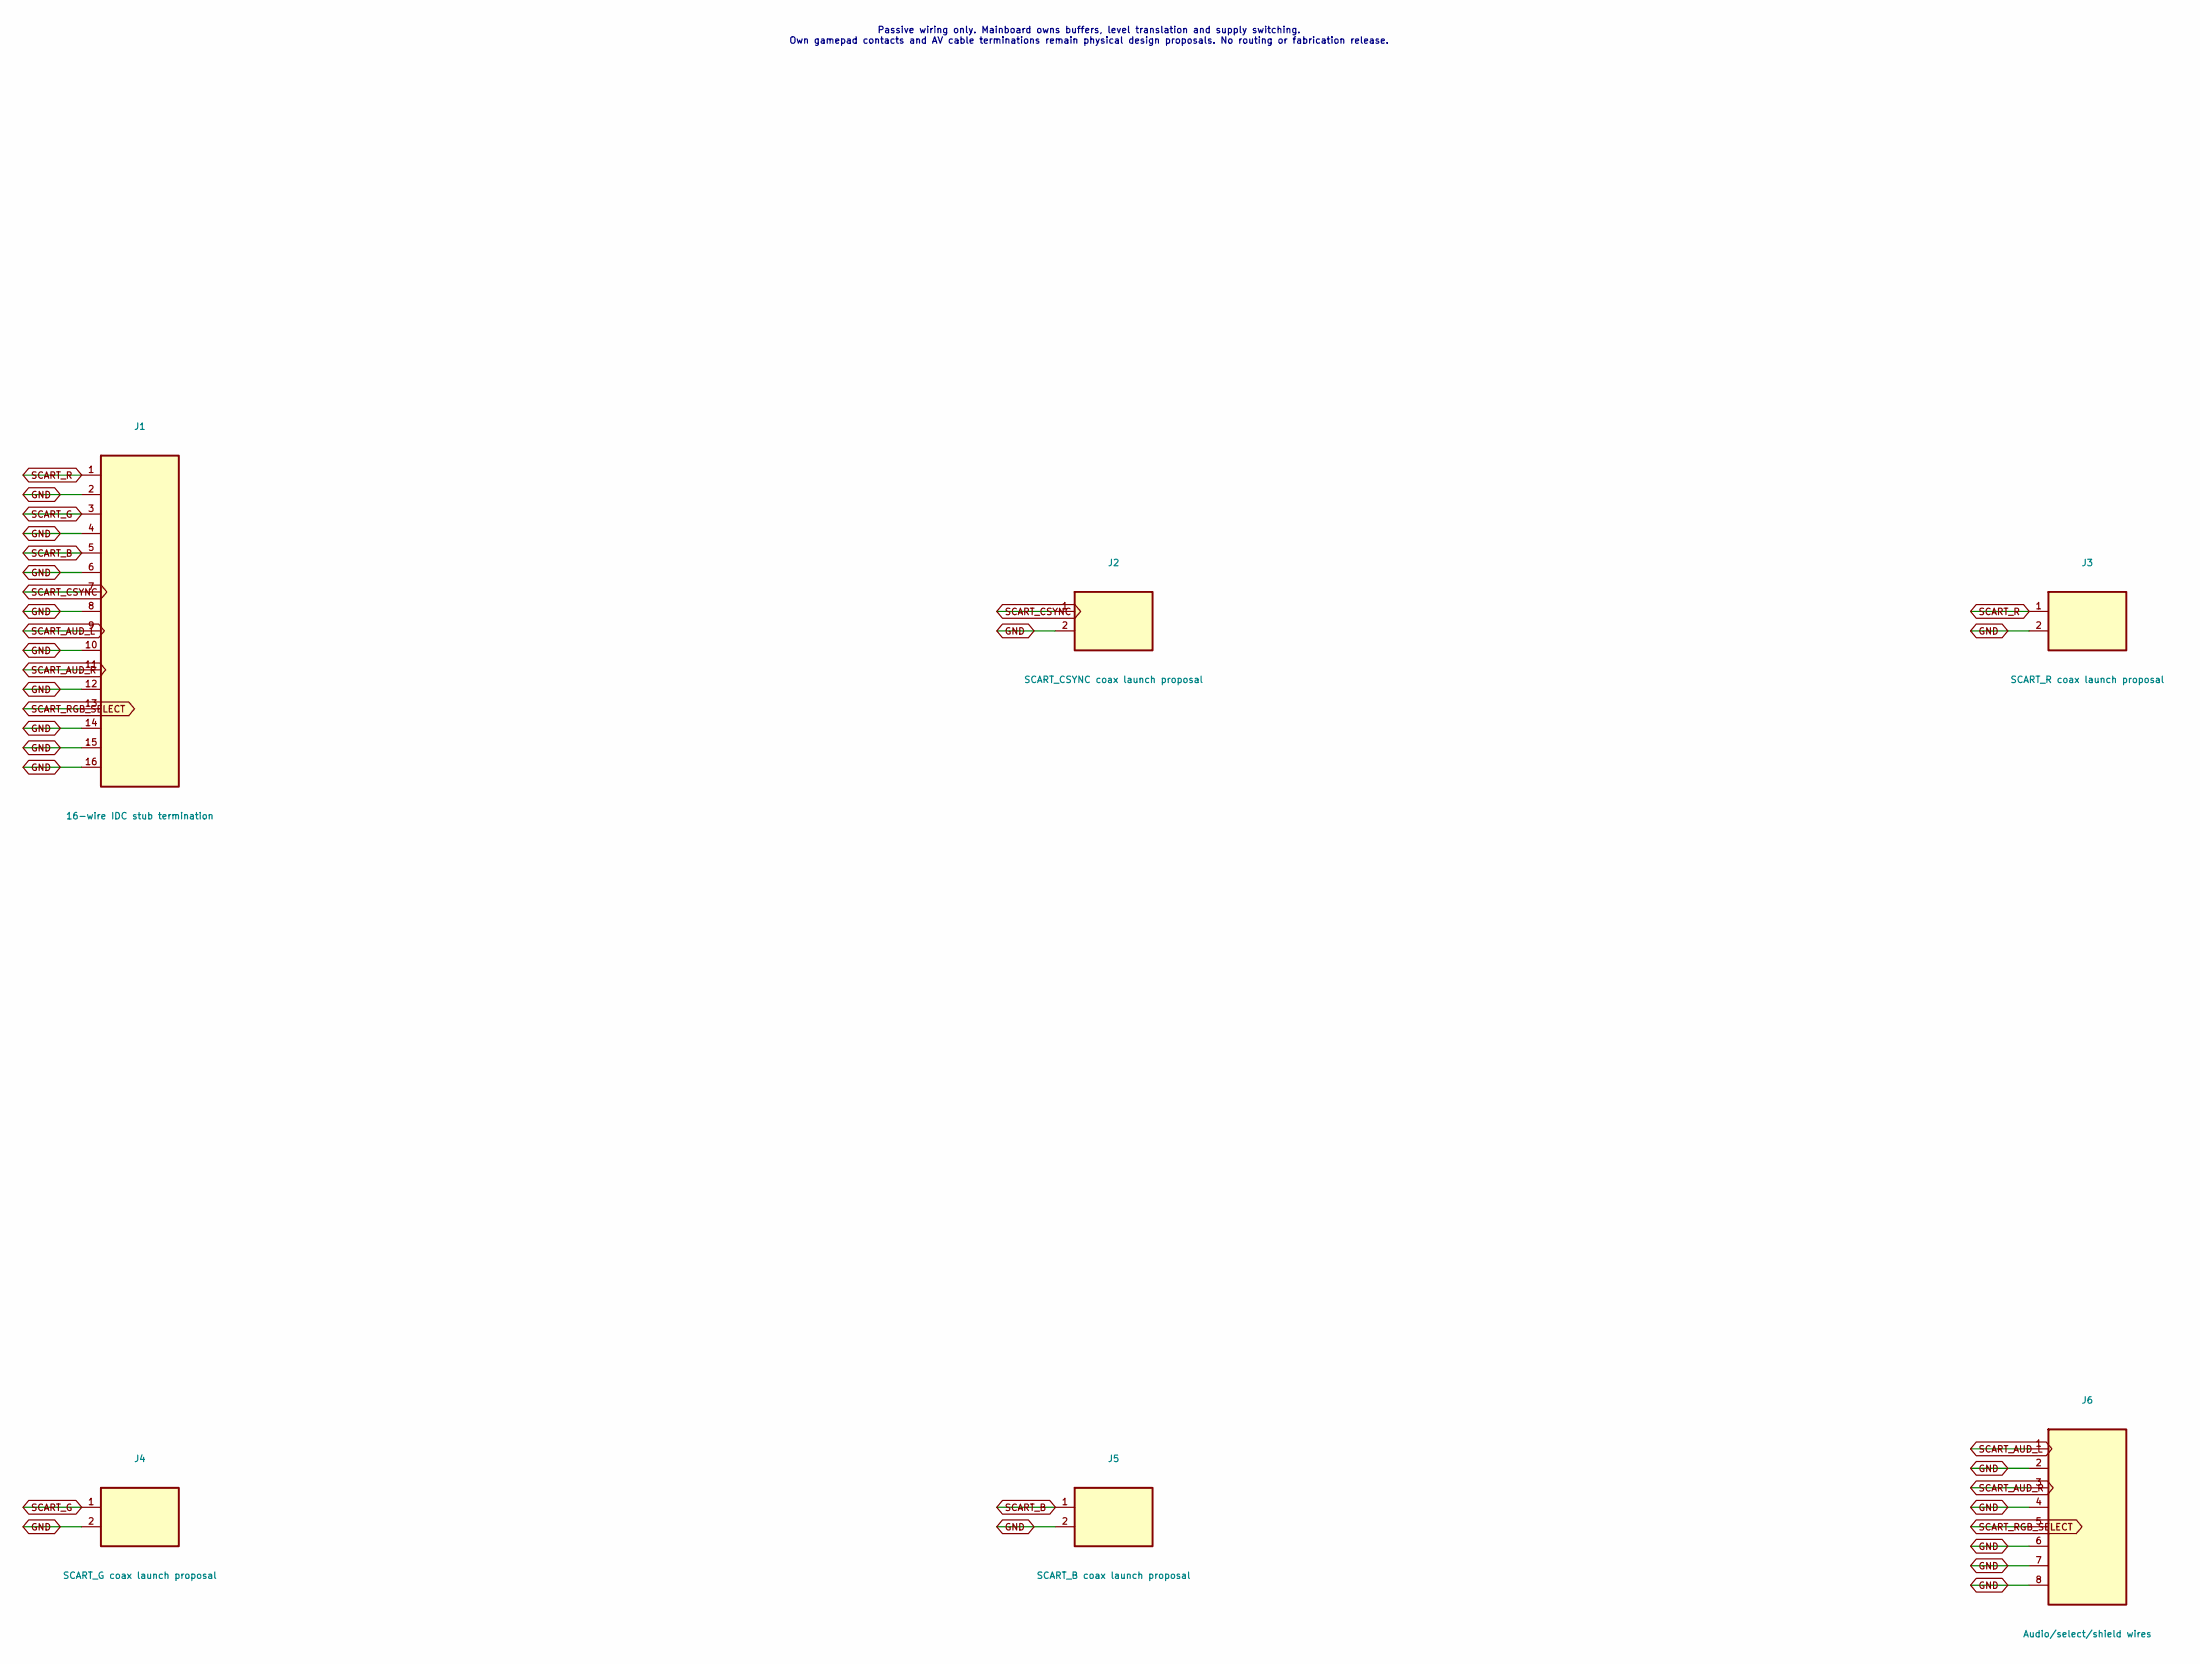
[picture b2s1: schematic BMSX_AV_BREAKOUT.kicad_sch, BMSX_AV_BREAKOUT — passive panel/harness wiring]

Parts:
J1: 16-wire IDC stub termination; Ribbon16_HandSolder_P1.27mm
J2: SCART_CSYNC coax launch proposal; Coax179_HandSolder_Launch
J3: SCART_R coax launch proposal; Coax179_HandSolder_Launch
J4: SCART_G coax launch proposal; Coax179_HandSolder_Launch
J5: SCART_B coax launch proposal; Coax179_HandSolder_Launch
J6: Audio/select/shield wires; Aux8_HandSolder_P1.00mm

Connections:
GND: J1.2, J1.4, J1.6, J1.8, J1.10, J1.12, J1.14, J1.15, J1.16, J2.2, J3.2, J4.2, J5.2, J6.2, J6.4, J6.6, J6.7, J6.8
SCART_AUD_L: J1.9, J6.1
SCART_AUD_R: J1.11, J6.3
SCART_B: J1.5, J5.1
SCART_CSYNC: J1.7, J2.1
SCART_G: J1.3, J4.1
SCART_R: J1.1, J3.1
SCART_RGB_SELECT: J1.13, J6.5

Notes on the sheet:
Passive wiring only. Mainboard owns buffers, level translation and supply switching. Own gamepad contacts and AV cable terminations remain physical design proposals. No routing or fabrication release.

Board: 4 copper layers, 8 parts (2 on the bottom side), 8 nets, no tracks yet.

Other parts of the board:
H1, H2: MountingHole_2.2mm

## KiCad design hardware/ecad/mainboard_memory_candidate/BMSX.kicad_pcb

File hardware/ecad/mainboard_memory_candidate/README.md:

# Memory expansion schematic candidate

This is a separate copy of the existing mainboard project. The schematic adds
U150/U151 private DRAM, U152/U153 snapshot SRAM, their supply bypass capacitors
and a snapshot-select pull-up. U1.50 and U1.101 drive the private RAS and OE;
U2.102 drives the snapshot select. The existing U2.174–U7.62 display-context
link and U7 INPUT remain unchanged.

The separate candidate PCB now contains the four memory devices, twelve
bypass capacitors and select pull-up from this schematic. Their pads and the
three modified ASIC pads carry the corresponding schematic nets. The grouped
placement moves U30 and C500–C502 by 4.5 mm; the remaining baseline footprints
and board outline are retained. There are no tracks, and the 19 inherited zones
are unfilled. This is an unrouted placement, not a DRC, power, signal-timing,
three-dimensional fit or manufacturing qualification. INPUT remains on U7.

To regenerate the candidate PCB from the untouched baseline and the current
candidate XML netlist, run `python3 hardware/tools/sync_memory_candidate.py`
with KiCad's `pcbnew` Python. Its output is written under `hardware/build/`;
no original board is modified. Copy the staged result into this project only
after reviewing it.

The baseline project under `../mainboard/` is preserved. Candidate schematic
PDF and KiCad XML netlist are distributed separately in the exports directory.

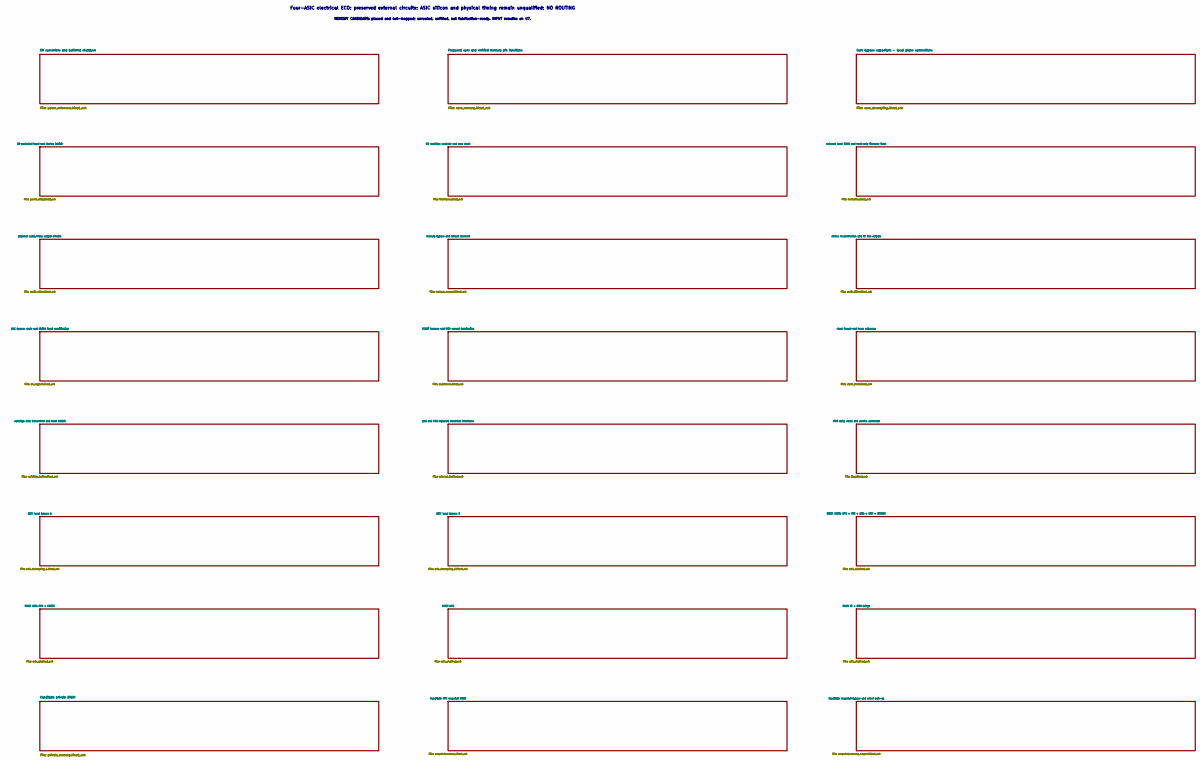
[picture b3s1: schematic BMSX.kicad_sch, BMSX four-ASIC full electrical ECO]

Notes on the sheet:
Four-ASIC electrical ECO; preserved external circuits; ASIC silicon and physical timing remain unqualified; NO ROUTING
MEMORY CANDIDATE: placed and net-mapped; unrouted, unfilled, not fabrication-ready. INPUT remains on U7.
